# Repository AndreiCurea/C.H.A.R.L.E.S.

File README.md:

# C.H.A.R.L.E.S.
Combustion Hazzard Autonomous Robot for Localization and Environmental Scanning

A hobby project of mine that involves building up an exploration robot from scratch, using different types of technologies. The purpose of this project is to monitor VOCs and other harmful gases in office/industrial buildings, while also creating a map of the surroundings to plot the acquired data on it.

I desired it to have LiDAR, ROS implementation, main computer board and high modularity when it comes to the electrical/mechanical parts.

It has custom PCBs, custom 3D parts, and code for the microcontrollers and the main computer.

Currently, the project only works remote controlled, as I've yet to develop the automation part of the code.

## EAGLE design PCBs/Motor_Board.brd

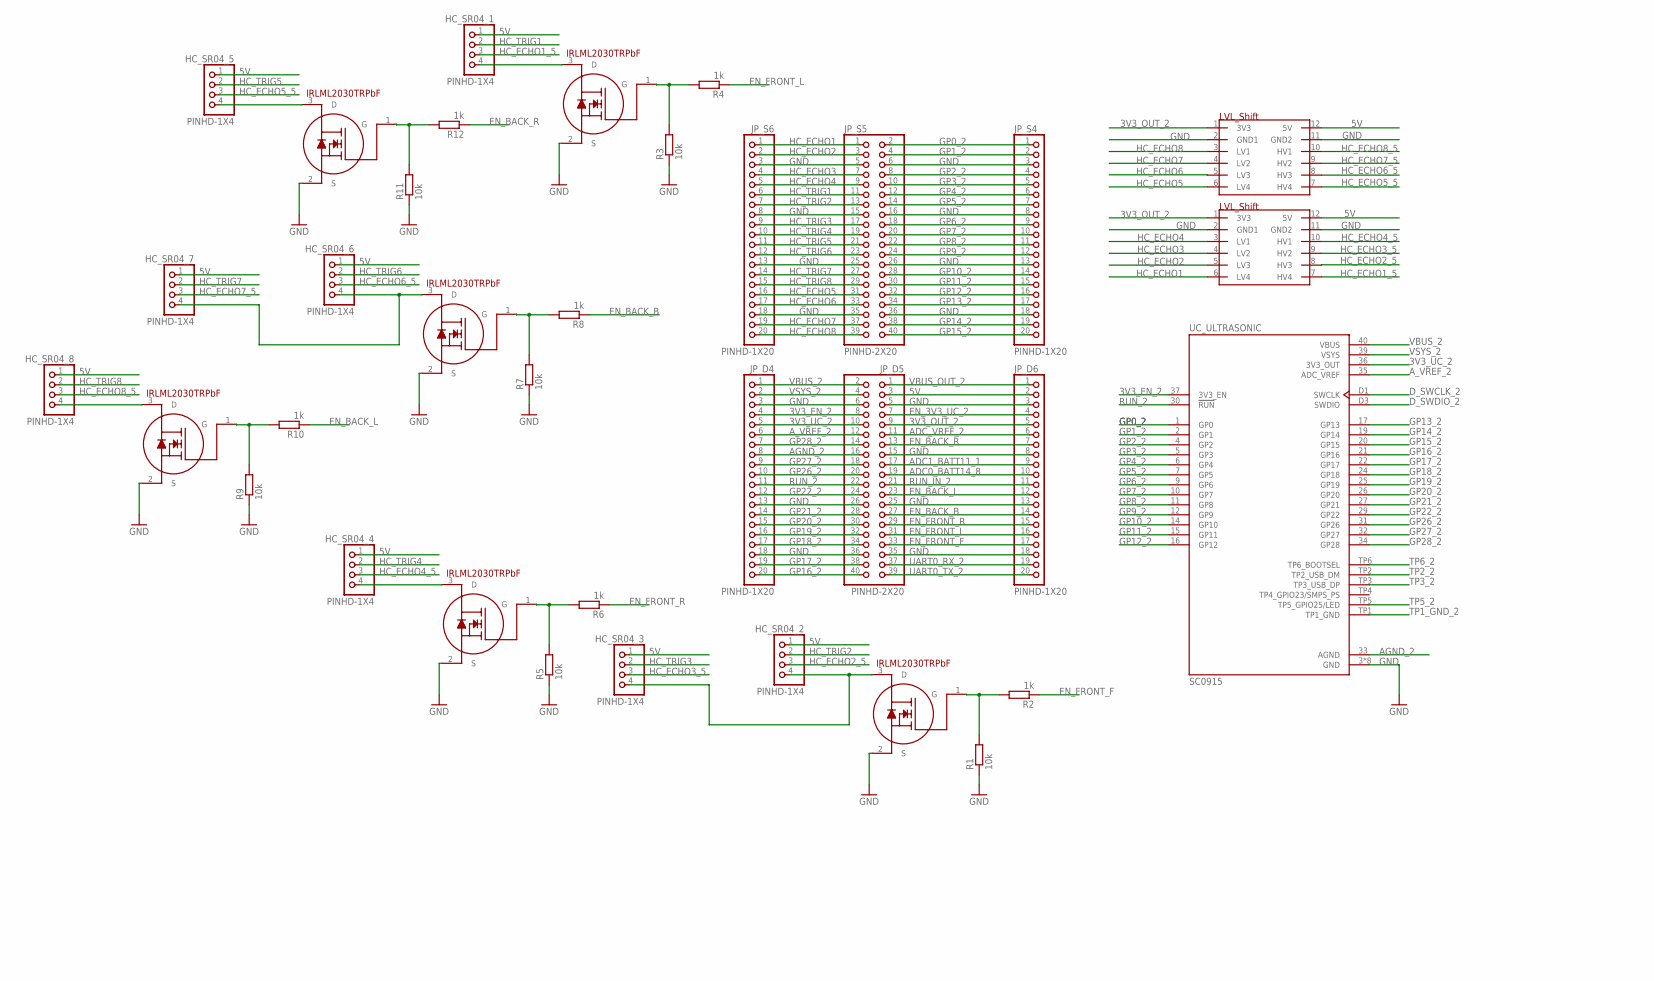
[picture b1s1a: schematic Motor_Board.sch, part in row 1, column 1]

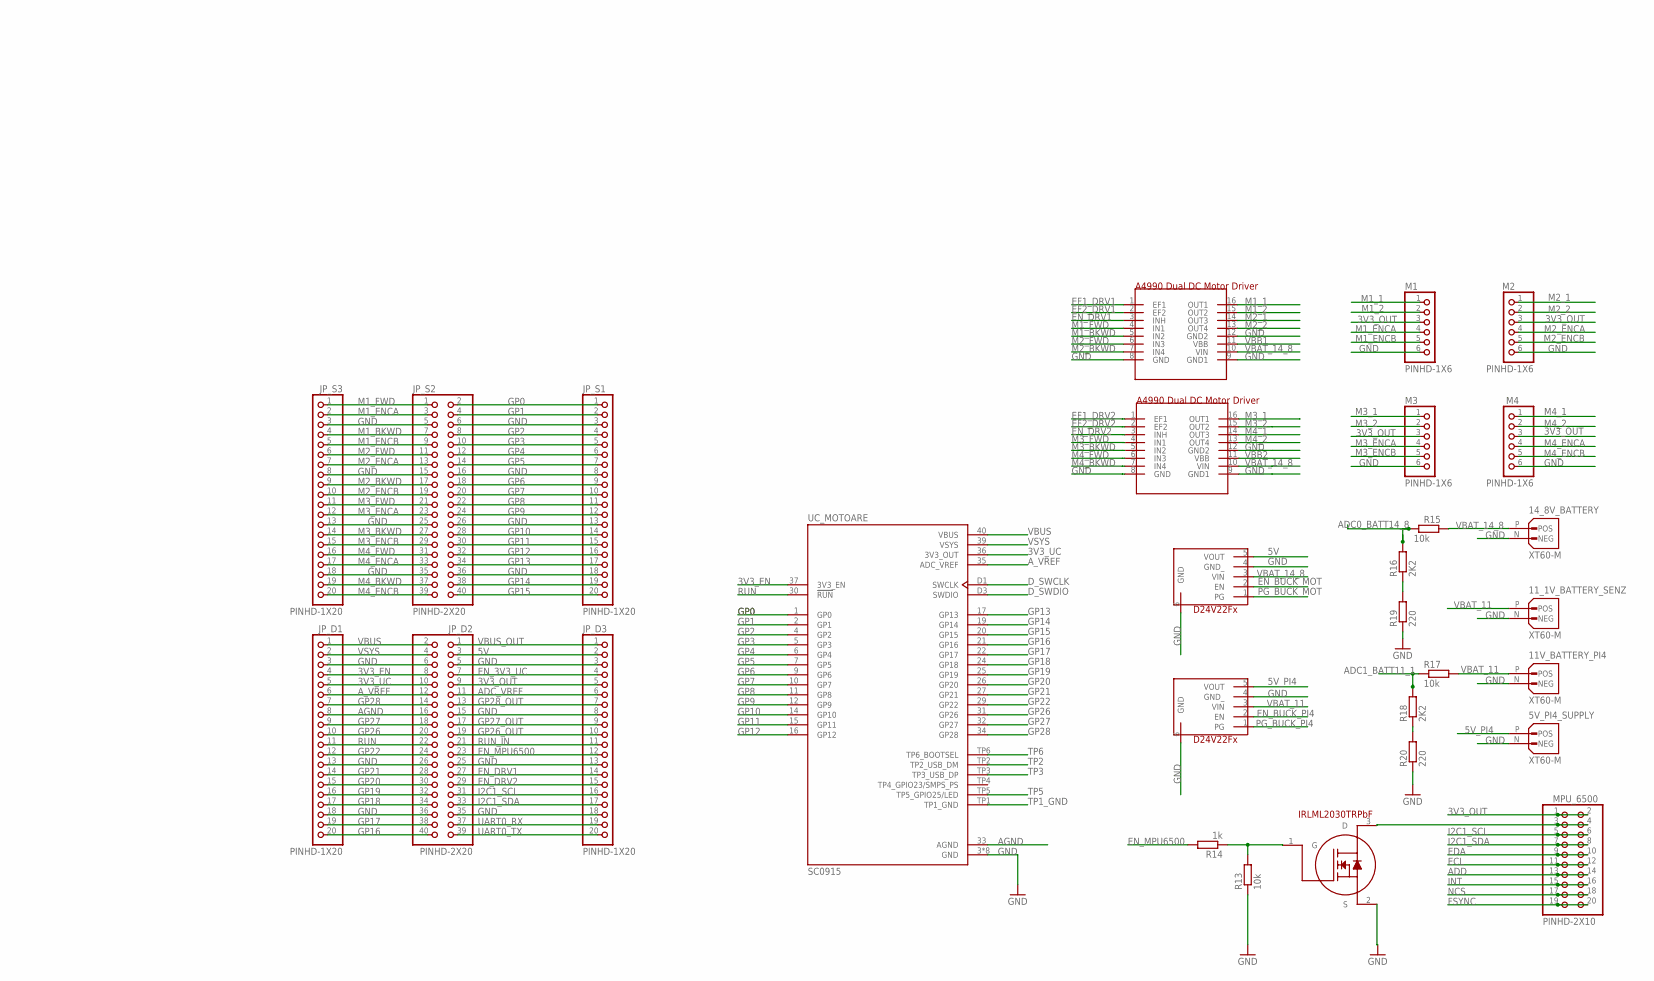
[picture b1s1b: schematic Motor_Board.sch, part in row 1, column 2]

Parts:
5V_PI4_SUPPLY, 11V_BATTERY_PI4, 11_1V_BATTERY_SENZ, 14_8V_BATTERY: XT60-M; AMASS_XT60-M
BUCK_5V, BUCK_5V1: POLOLU_BUCK_CONVERTER; POLOLU_BUCK_FOOTPRINT
DRV1, DRV2: A4990_DUAL; A4990_FOOTPRINT
HC_SR04_1, HC_SR04_2, HC_SR04_3, HC_SR04_4, HC_SR04_5, HC_SR04_6, HC_SR04_7, HC_SR04_8: PINHD-1X4; 1X04
JP_D1, JP_D3, JP_D4, JP_D6: PINHD-1X20; 1X20
JP_D2, JP_D5: PINHD-2X20; 2X20
JP_S1, JP_S3, JP_S4, JP_S6: PINHD-1X20; 1X20
JP_S2, JP_S5: PINHD-2X20; 2X20
M1, M2, M3, M4: PINHD-1X6; 1X06
MPU_6500: PINHD-2X10; 2X10
R1, R3, R5, R7, R9, R11, R13, R15, R17: 10k; R0805
R2, R4, R6, R8, R10, R12, R14: 1k; R0805
R16, R18: 2K2; R0805
R19, R20: 220; R0805
U$1, U$2: 4_CH_BIDIRECTIONAL_LVL_SHIFTER; LVL_SHIFT_FOOTPRINT
U$8, U$9, U$10, U$11, U$12, U$13, U$14: IRLML2030TRBRBF_NMOS; IRLML2030TRPBF_FOOTPRINT
UC_MOTOARE: SC0915; MODULE_SC0915
UC_ULTRASONIC: SC0915; MODULE_SC0915

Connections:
3V3_EN: JP_D1.4, JP_D2.8, UC_MOTOARE.37 (3V3_EN)
3V3_EN_2: JP_D4.4, JP_D5.8, UC_ULTRASONIC.37 (3V3_EN)
3V3_OUT: JP_D2.9, JP_D3.5, M1.3, M2.3, M3.3, M4.3, MPU_6500.1, MPU_6500.2
3V3_OUT_2: JP_D5.9, JP_D6.5, U$1.1 (3V3), U$2.1 (3V3)
3V3_UC: JP_D1.5, JP_D2.10, UC_MOTOARE.36 (3V3_OUT)
3V3_UC_2: JP_D4.5, JP_D5.10, UC_ULTRASONIC.36 (3V3_OUT)
5V: BUCK_5V.5 (VOUT), HC_SR04_1.1, HC_SR04_2.1, HC_SR04_3.1, HC_SR04_4.1, HC_SR04_5.1, HC_SR04_6.1, HC_SR04_7.1, HC_SR04_8.1, JP_D2.3, JP_D3.2, JP_D5.3, JP_D6.2, U$1.12 (5V), U$2.12 (5V)
5V_PI4: 5V_PI4_SUPPLY.P (POS), BUCK_5V1.5 (VOUT)
ADC0_BATT14_8: JP_D5.19, JP_D6.10, R15.1, R16.2
ADC1_BATT11_1: JP_D5.17, JP_D6.9, R17.1, R18.2
ADC_VREF: JP_D2.11, JP_D3.6
ADC_VREF_2: JP_D5.11, JP_D6.6
ADD: MPU_6500.13, MPU_6500.14
AGND: JP_D1.8, JP_D2.16, UC_MOTOARE.33 (AGND)
AGND_2: JP_D4.8, JP_D5.16, UC_ULTRASONIC.33 (AGND)
A_VREF: JP_D1.6, JP_D2.12, UC_MOTOARE.35 (ADC_VREF)
A_VREF_2: JP_D4.6, JP_D5.12, UC_ULTRASONIC.35 (ADC_VREF)
D_SWCLK: UC_MOTOARE.D1 (SWCLK)
D_SWCLK_2: UC_ULTRASONIC.D1 (SWCLK)
D_SWDIO: UC_MOTOARE.D3 (SWDIO)
D_SWDIO_2: UC_ULTRASONIC.D3 (SWDIO)
ECL: MPU_6500.11, MPU_6500.12
EDA: MPU_6500.9, MPU_6500.10
EF1_DRV1: DRV1.1 (EF1)
EF1_DRV2: DRV2.1 (EF1)
EF2_DRV1: DRV1.2 (EF2)
EF2_DRV2: DRV2.2 (EF2)
EN_3V3_UC: JP_D2.7, JP_D3.4
EN_3V3_UC_2: JP_D5.7, JP_D6.4
EN_BACK_B: JP_D5.27, JP_D6.14, R8.1
EN_BACK_L: JP_D5.23, JP_D6.12, R10.1
EN_BACK_R: JP_D5.13, JP_D6.7, R12.1
EN_BUCK_MOT: BUCK_5V.2 (EN)
EN_BUCK_PI4: BUCK_5V1.2 (EN)
EN_DRV1: DRV1.3 (INH), JP_D2.27, JP_D3.14
EN_DRV2: DRV2.3 (INH), JP_D2.29, JP_D3.15
EN_FRONT_F: JP_D5.33, JP_D6.17, R2.1
EN_FRONT_L: JP_D5.31, JP_D6.16, R4.1
EN_FRONT_R: JP_D5.29, JP_D6.15, R6.1
EN_MPU6500: JP_D2.23, JP_D3.12, R14.2
FSYNC: MPU_6500.19, MPU_6500.20
GND: 5V_PI4_SUPPLY.N (NEG), 11V_BATTERY_PI4.N (NEG), 11_1V_BATTERY_SENZ.N (NEG), 14_8V_BATTERY.N (NEG), BUCK_5V.4 (GND_), BUCK_5V.6 (GND), BUCK_5V1.4 (GND_), BUCK_5V1.6 (GND), DRV1.8 (GND), DRV1.9 (GND1), DRV1.12 (GND2), DRV2.8 (GND), DRV2.9 (GND1), DRV2.12 (GND2), JP_D1.3, JP_D1.13, JP_D1.18, JP_D2.5, JP_D2.6, JP_D2.15, JP_D2.25, JP_D2.26, JP_D2.35, JP_D2.36, JP_D3.3, JP_D3.8, JP_D3.13, JP_D3.18, JP_D4.3, JP_D4.13, JP_D4.18, JP_D5.5, JP_D5.6, JP_D5.15, JP_D5.25, JP_D5.26, JP_D5.35, JP_D5.36, JP_D6.3, JP_D6.8, JP_D6.13, JP_D6.18, JP_S1.3, JP_S1.8, JP_S1.13, JP_S1.18, JP_S2.5, JP_S2.6, JP_S2.15, JP_S2.16, JP_S2.25, JP_S2.26, JP_S2.35, JP_S2.36, JP_S3.3, JP_S3.8, JP_S3.13, JP_S3.18, JP_S4.3, JP_S4.8, JP_S4.13, JP_S4.18, JP_S5.5, JP_S5.6, JP_S5.15, JP_S5.16, JP_S5.25, JP_S5.26, JP_S5.35, JP_S5.36, JP_S6.3, JP_S6.8, JP_S6.13, JP_S6.18, M1.6, M2.6, M3.6, M4.6, R1.1, R3.1, R5.1, R7.1, R9.1, R11.1, R13.1, R19.1, R20.1, U$1.2 (GND1), U$1.11 (GND2), U$2.2 (GND1), U$2.11 (GND2), U$8.2 (S), U$9.2 (S), U$10.2 (S), U$11.2 (S), U$12.2 (S), U$13.2 (S), U$14.2 (S), UC_MOTOARE.3 (GND), UC_MOTOARE.8 (GND)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
GP0: JP_S1.1, JP_S2.2, UC_MOTOARE.1 (GP0)
GP0_2: JP_S4.1, JP_S5.2, UC_ULTRASONIC.1 (GP0)
GP1: JP_S1.2, JP_S2.4, UC_MOTOARE.2 (GP1)
GP1_2: JP_S4.2, JP_S5.4, UC_ULTRASONIC.2 (GP1)
GP2: JP_S1.4, JP_S2.8, UC_MOTOARE.4 (GP2)
GP2_2: JP_S4.4, JP_S5.8, UC_ULTRASONIC.4 (GP2)
GP3: JP_S1.5, JP_S2.10, UC_MOTOARE.5 (GP3)
GP3_2: JP_S4.5, JP_S5.10, UC_ULTRASONIC.5 (GP3)
GP4: JP_S1.6, JP_S2.12, UC_MOTOARE.6 (GP4)
GP4_2: JP_S4.6, JP_S5.12, UC_ULTRASONIC.6 (GP4)
GP5: JP_S1.7, JP_S2.14, UC_MOTOARE.7 (GP5)
GP5_2: JP_S4.7, JP_S5.14, UC_ULTRASONIC.7 (GP5)
GP6: JP_S1.9, JP_S2.18, UC_MOTOARE.9 (GP6)
GP6_2: JP_S4.9, JP_S5.18, UC_ULTRASONIC.9 (GP6)
GP7: JP_S1.10, JP_S2.20, UC_MOTOARE.10 (GP7)
GP7_2: JP_S4.10, JP_S5.20, UC_ULTRASONIC.10 (GP7)
GP8: JP_S1.11, JP_S2.22, UC_MOTOARE.11 (GP8)
GP8_2: JP_S4.11, JP_S5.22, UC_ULTRASONIC.11 (GP8)
GP9: JP_S1.12, JP_S2.24, UC_MOTOARE.12 (GP9)
GP9_2: JP_S4.12, JP_S5.24, UC_ULTRASONIC.12 (GP9)
GP10: JP_S1.14, JP_S2.28, UC_MOTOARE.14 (GP10)
GP10_2: JP_S4.14, JP_S5.28, UC_ULTRASONIC.14 (GP10)
GP11: JP_S1.15, JP_S2.30, UC_MOTOARE.15 (GP11)
GP11_2: JP_S4.15, JP_S5.30, UC_ULTRASONIC.15 (GP11)
GP12: JP_S1.16, JP_S2.32, UC_MOTOARE.16 (GP12)
GP12_2: JP_S4.16, JP_S5.32, UC_ULTRASONIC.16 (GP12)
GP13: JP_S1.17, JP_S2.34, UC_MOTOARE.17 (GP13)
GP13_2: JP_S4.17, JP_S5.34, UC_ULTRASONIC.17 (GP13)
GP14: JP_S1.19, JP_S2.38, UC_MOTOARE.19 (GP14)
GP14_2: JP_S4.19, JP_S5.38, UC_ULTRASONIC.19 (GP14)
GP15: JP_S1.20, JP_S2.40, UC_MOTOARE.20 (GP15)
GP15_2: JP_S4.20, JP_S5.40, UC_ULTRASONIC.20 (GP15)
GP16: JP_D1.20, JP_D2.40, UC_MOTOARE.21 (GP16)
GP16_2: JP_D4.20, JP_D5.40, UC_ULTRASONIC.21 (GP16)
GP17: JP_D1.19, JP_D2.38, UC_MOTOARE.22 (GP17)
GP17_2: JP_D4.19, JP_D5.38, UC_ULTRASONIC.22 (GP17)
GP18: JP_D1.17, JP_D2.34, UC_MOTOARE.24 (GP18)
GP18_2: JP_D4.17, JP_D5.34, UC_ULTRASONIC.24 (GP18)
GP19: JP_D1.16, JP_D2.32, UC_MOTOARE.25 (GP19)
GP19_2: JP_D4.16, JP_D5.32, UC_ULTRASONIC.25 (GP19)
GP20: JP_D1.15, JP_D2.30, UC_MOTOARE.26 (GP20)
GP20_2: JP_D4.15, JP_D5.30, UC_ULTRASONIC.26 (GP20)
GP21: JP_D1.14, JP_D2.28, UC_MOTOARE.27 (GP21)
GP21_2: JP_D4.14, JP_D5.28, UC_ULTRASONIC.27 (GP21)
GP22: JP_D1.12, JP_D2.24, UC_MOTOARE.29 (GP22)
GP22_2: JP_D4.12, JP_D5.24, UC_ULTRASONIC.29 (GP22)
GP26: JP_D1.10, JP_D2.20, UC_MOTOARE.31 (GP26)
GP26_2: JP_D4.10, JP_D5.20, UC_ULTRASONIC.31 (GP26)
GP26_OUT: JP_D2.19, JP_D3.10
GP27: JP_D1.9, JP_D2.18, UC_MOTOARE.32 (GP27)
GP27_2: JP_D4.9, JP_D5.18, UC_ULTRASONIC.32 (GP27)
GP27_OUT: JP_D2.17, JP_D3.9
GP28: JP_D1.7, JP_D2.14, UC_MOTOARE.34 (GP28)
GP28_2: JP_D4.7, JP_D5.14, UC_ULTRASONIC.34 (GP28)
GP28_OUT: JP_D2.13, JP_D3.7
HC_ECHO1: JP_S5.1, JP_S6.1, U$2.6 (LV4)
HC_ECHO1_5: HC_SR04_1.3, U$2.7 (HV4)
HC_ECHO2: JP_S5.3, JP_S6.2, U$2.5 (LV3)
HC_ECHO2_5: HC_SR04_2.3, U$2.8 (HV3)
HC_ECHO3: JP_S5.7, JP_S6.4, U$2.4 (LV2)
HC_ECHO3_5: HC_SR04_3.3, U$2.9 (HV2)
HC_ECHO4: JP_S5.9, JP_S6.5, U$2.3 (LV1)
HC_ECHO4_5: HC_SR04_4.3, U$2.10 (HV1)
HC_ECHO5: JP_S5.31, JP_S6.16, U$1.6 (LV4)
HC_ECHO5_5: HC_SR04_5.3, U$1.7 (HV4)
HC_ECHO6: JP_S5.33, JP_S6.17, U$1.5 (LV3)
HC_ECHO6_5: HC_SR04_6.3, U$1.8 (HV3)
HC_ECHO7: JP_S5.37, JP_S6.19, U$1.4 (LV2)
HC_ECHO7_5: HC_SR04_7.3, U$1.9 (HV2)
HC_ECHO8: JP_S5.39, JP_S6.20, U$1.3 (LV1)
HC_ECHO8_5: HC_SR04_8.3, U$1.10 (HV1)
HC_TRIG1: HC_SR04_1.2, JP_S5.11, JP_S6.6
HC_TRIG2: HC_SR04_2.2, JP_S5.13, JP_S6.7
HC_TRIG3: HC_SR04_3.2, JP_S5.17, JP_S6.9
HC_TRIG4: HC_SR04_4.2, JP_S5.19, JP_S6.10
HC_TRIG5: HC_SR04_5.2, JP_S5.21, JP_S6.11
HC_TRIG6: HC_SR04_6.2, JP_S5.23, JP_S6.12
HC_TRIG7: HC_SR04_7.2, JP_S5.27, JP_S6.14
HC_TRIG8: HC_SR04_8.2, JP_S5.29, JP_S6.15
I2C1_SCL: JP_D2.31, JP_D3.16, MPU_6500.5, MPU_6500.6
I2C1_SDA: JP_D2.33, JP_D3.17, MPU_6500.7, MPU_6500.8
INT: MPU_6500.15, MPU_6500.16
M1_1: DRV1.16 (OUT1), M1.1
M1_2: DRV1.15 (OUT2), M1.2
M1_BKWD: DRV1.5 (IN2), JP_S2.7, JP_S3.4
M1_ENCA: JP_S2.3, JP_S3.2, M1.4
M1_ENCB: JP_S2.9, JP_S3.5, M1.5
M1_FWD: DRV1.4 (IN1), JP_S2.1, JP_S3.1
M2_1: DRV1.14 (OUT3), M2.1
M2_2: DRV1.13 (OUT4), M2.2
M2_BKWD: DRV1.7 (IN4), JP_S2.17, JP_S3.9
M2_ENCA: JP_S2.13, JP_S3.7, M2.4
M2_ENCB: JP_S2.19, JP_S3.10, M2.5
M2_FWD: DRV1.6 (IN3), JP_S2.11, JP_S3.6
M3_1: DRV2.16 (OUT1), M3.1
M3_2: DRV2.15 (OUT2), M3.2
M3_BKWD: DRV2.5 (IN2), JP_S2.27, JP_S3.14
M3_ENCA: JP_S2.23, JP_S3.12, M3.4
M3_ENCB: JP_S2.29, JP_S3.15, M3.5
M3_FWD: DRV2.4 (IN1), JP_S2.21, JP_S3.11
M4_1: DRV2.14 (OUT3), M4.1
M4_2: DRV2.13 (OUT4), M4.2
M4_BKWD: DRV2.7 (IN4), JP_S2.37, JP_S3.19
M4_ENCA: JP_S2.33, JP_S3.17, M4.4
M4_ENCB: JP_S2.39, JP_S3.20, M4.5
M4_FWD: DRV2.6 (IN3), JP_S2.31, JP_S3.16
unnamed: HC_SR04_1.4, U$9.3 (D)
unnamed: R3.2, R4.2, U$9.1 (G)
unnamed: HC_SR04_2.4, HC_SR04_3.4, U$10.3 (D)
unnamed: R1.2, R2.2, U$10.1 (G)
unnamed: HC_SR04_4.4, U$11.3 (D)
unnamed: R5.2, R6.2, U$11.1 (G)
unnamed: HC_SR04_5.4, U$12.3 (D)
unnamed: R11.2, R12.2, U$12.1 (G)
unnamed: R7.2, R8.2, U$13.1 (G)
unnamed: HC_SR04_6.4, HC_SR04_7.4, U$13.3 (D)
unnamed: HC_SR04_8.4, U$14.3 (D)
unnamed: R9.2, R10.2, U$14.1 (G)
unnamed: MPU_6500.3, MPU_6500.4, U$8.3 (D)
unnamed: R13.2, R14.1, U$8.1 (G)
unnamed: R16.1, R19.2
unnamed: R18.1, R20.2
NCS: MPU_6500.17, MPU_6500.18
PG_BUCK_MOT: BUCK_5V.1 (PG)
PG_BUCK_PI4: BUCK_5V1.1 (PG)
RUN: JP_D1.11, JP_D2.22, UC_MOTOARE.30 (!RUN)
RUN_2: JP_D4.11, JP_D5.22, UC_ULTRASONIC.30 (!RUN)
RUN_IN: JP_D2.21, JP_D3.11
RUN_IN_2: JP_D5.21, JP_D6.11
TP1_GND: UC_MOTOARE.TP1 (TP1_GND)
TP1_GND_2: UC_ULTRASONIC.TP1 (TP1_GND)
TP2: UC_MOTOARE.TP2 (TP2_USB_DM)
TP2_2: UC_ULTRASONIC.TP2 (TP2_USB_DM)
TP3: UC_MOTOARE.TP3 (TP3_USB_DP)
TP3_2: UC_ULTRASONIC.TP3 (TP3_USB_DP)
TP5: UC_MOTOARE.TP5 (TP5_GPIO25/LED)
TP5_2: UC_ULTRASONIC.TP5 (TP5_GPIO25/LED)
TP6: UC_MOTOARE.TP6 (TP6_BOOTSEL)
TP6_2: UC_ULTRASONIC.TP6 (TP6_BOOTSEL)
UART0_RX: JP_D2.37, JP_D3.19
UART0_RX_2: JP_D5.37, JP_D6.19
UART0_TX: JP_D2.39, JP_D3.20
UART0_TX_2: JP_D5.39, JP_D6.20
VBAT_11: 11V_BATTERY_PI4.P (POS), 11_1V_BATTERY_SENZ.P (POS), BUCK_5V1.3 (VIN), R17.2
VBAT_14_8: 14_8V_BATTERY.P (POS), BUCK_5V.3 (VIN), DRV1.10 (VIN), DRV2.10 (VIN), R15.2
VBB1: DRV1.11 (VBB)
VBB2: DRV2.11 (VBB)
VBUS: JP_D1.1, JP_D2.2, UC_MOTOARE.40 (VBUS)
VBUS_2: JP_D4.1, JP_D5.2, UC_ULTRASONIC.40 (VBUS)
VBUS_OUT: JP_D2.1, JP_D3.1
VBUS_OUT_2: JP_D5.1, JP_D6.1
VSYS: JP_D1.2, JP_D2.4, UC_MOTOARE.39 (VSYS)
VSYS_2: JP_D4.2, JP_D5.4, UC_ULTRASONIC.39 (VSYS)

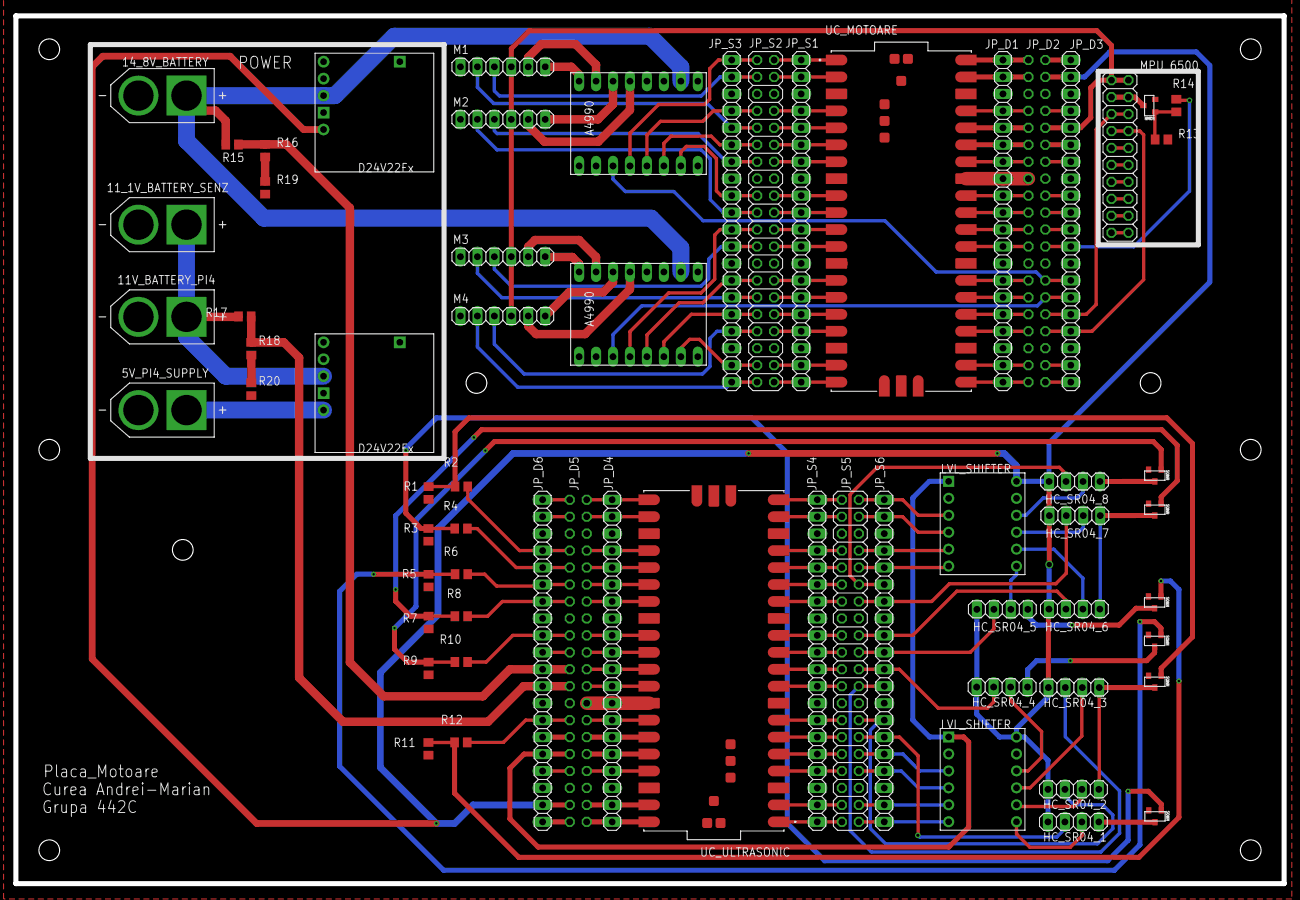
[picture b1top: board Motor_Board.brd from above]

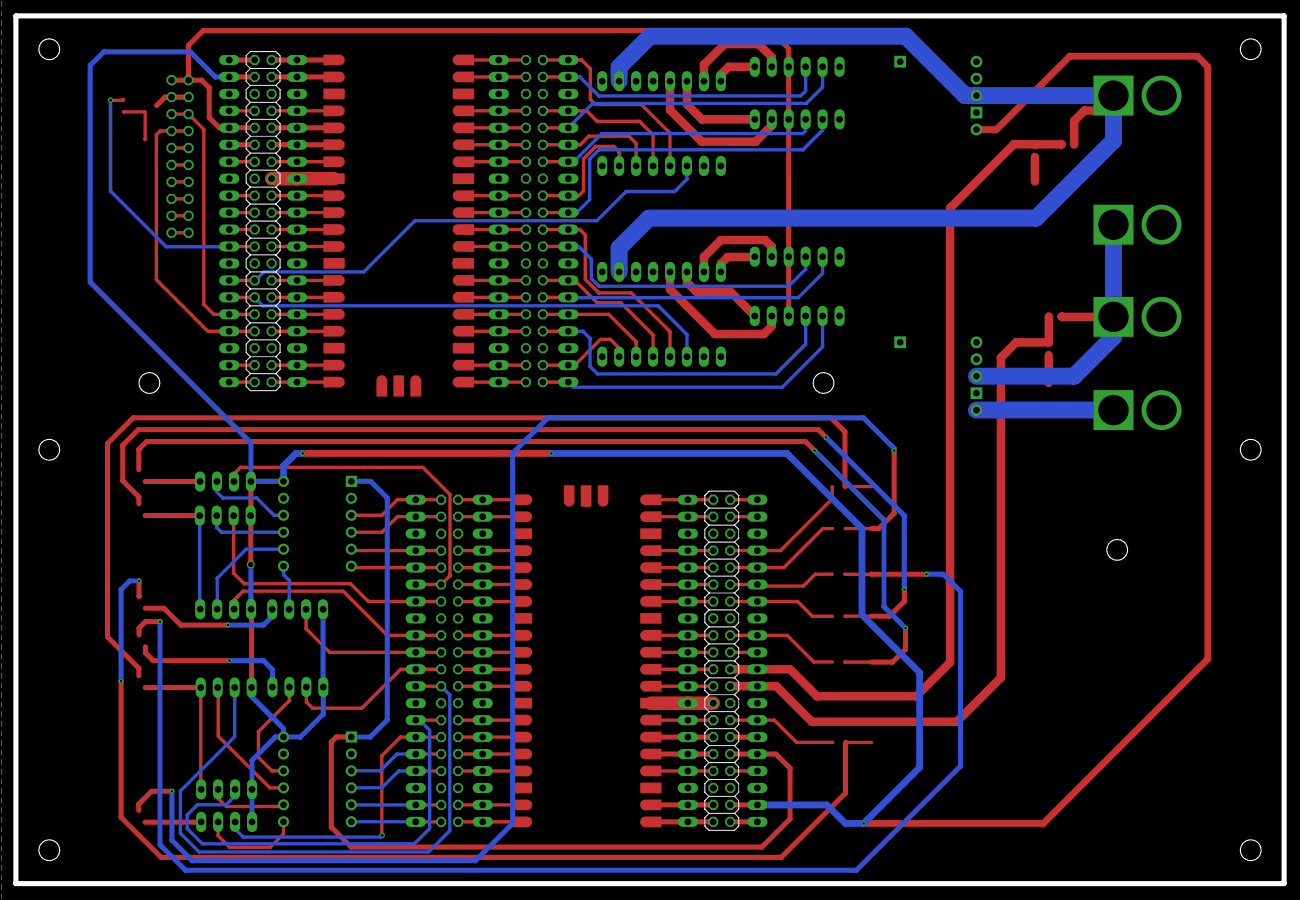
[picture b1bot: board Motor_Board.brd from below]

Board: 2 copper layers, 190.0 x 130.0 mm, 64 parts (2 on the bottom side), 171 nets.

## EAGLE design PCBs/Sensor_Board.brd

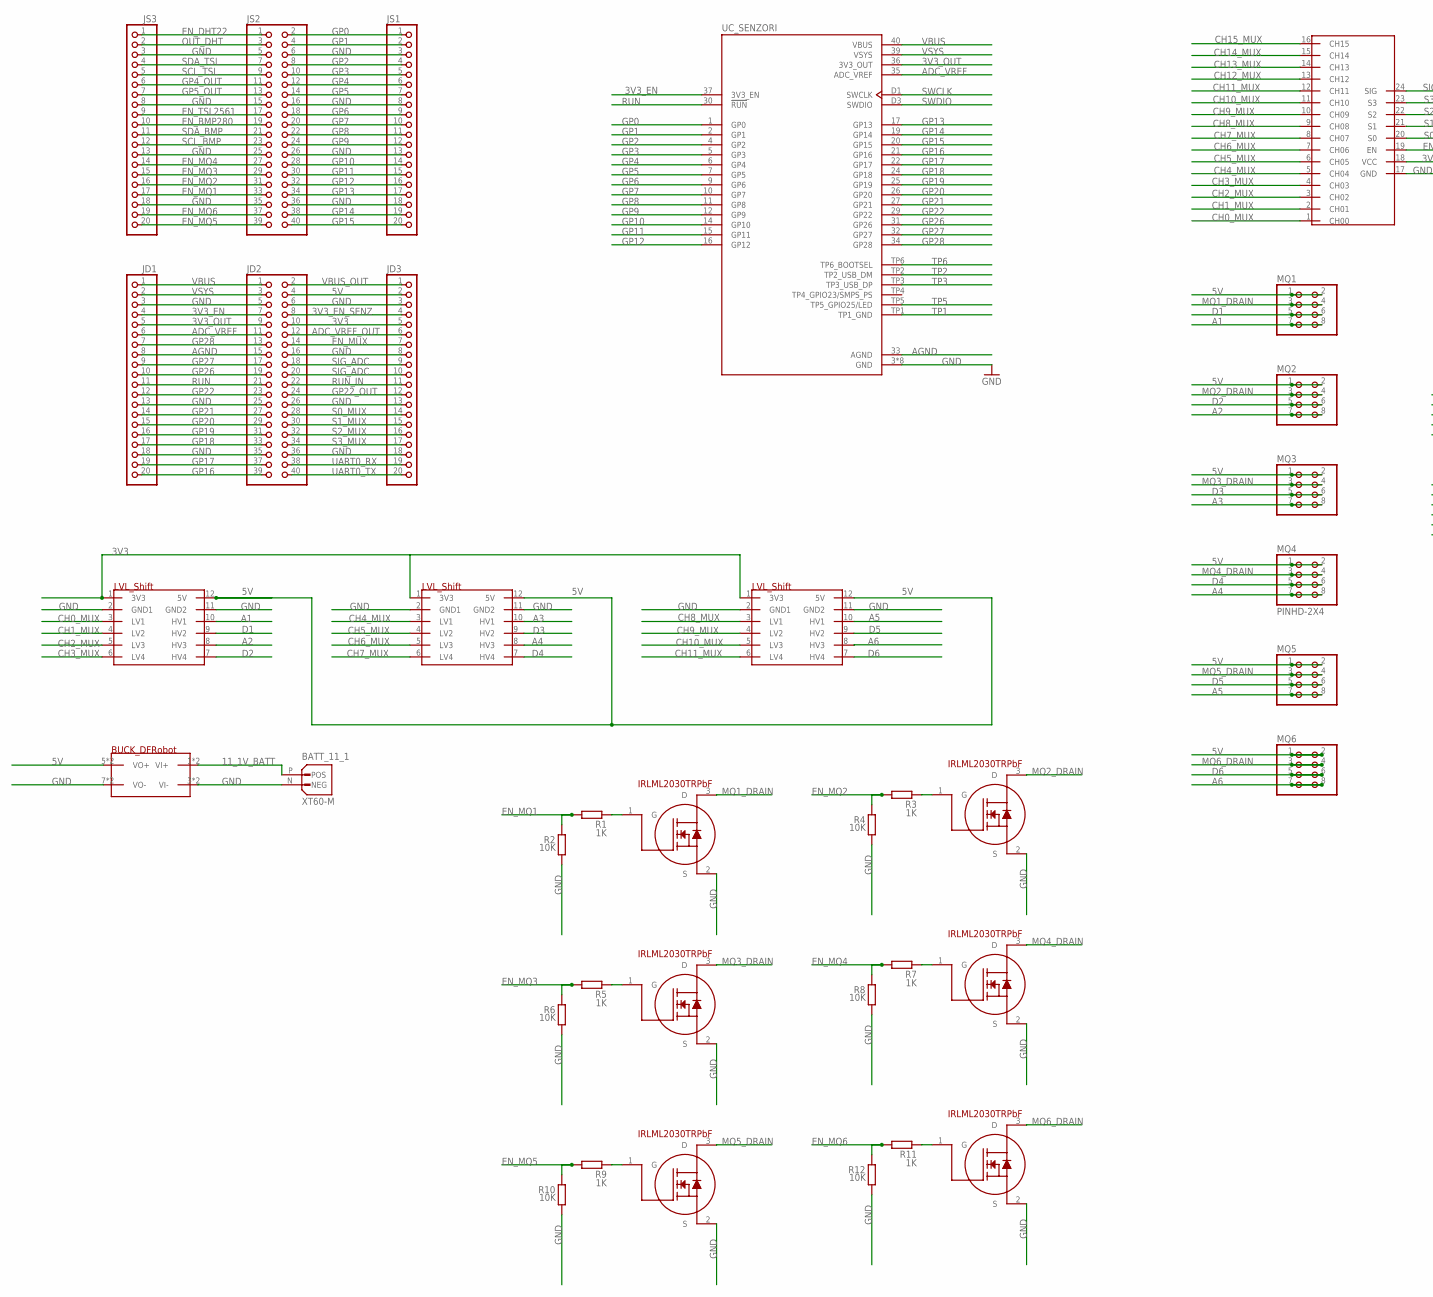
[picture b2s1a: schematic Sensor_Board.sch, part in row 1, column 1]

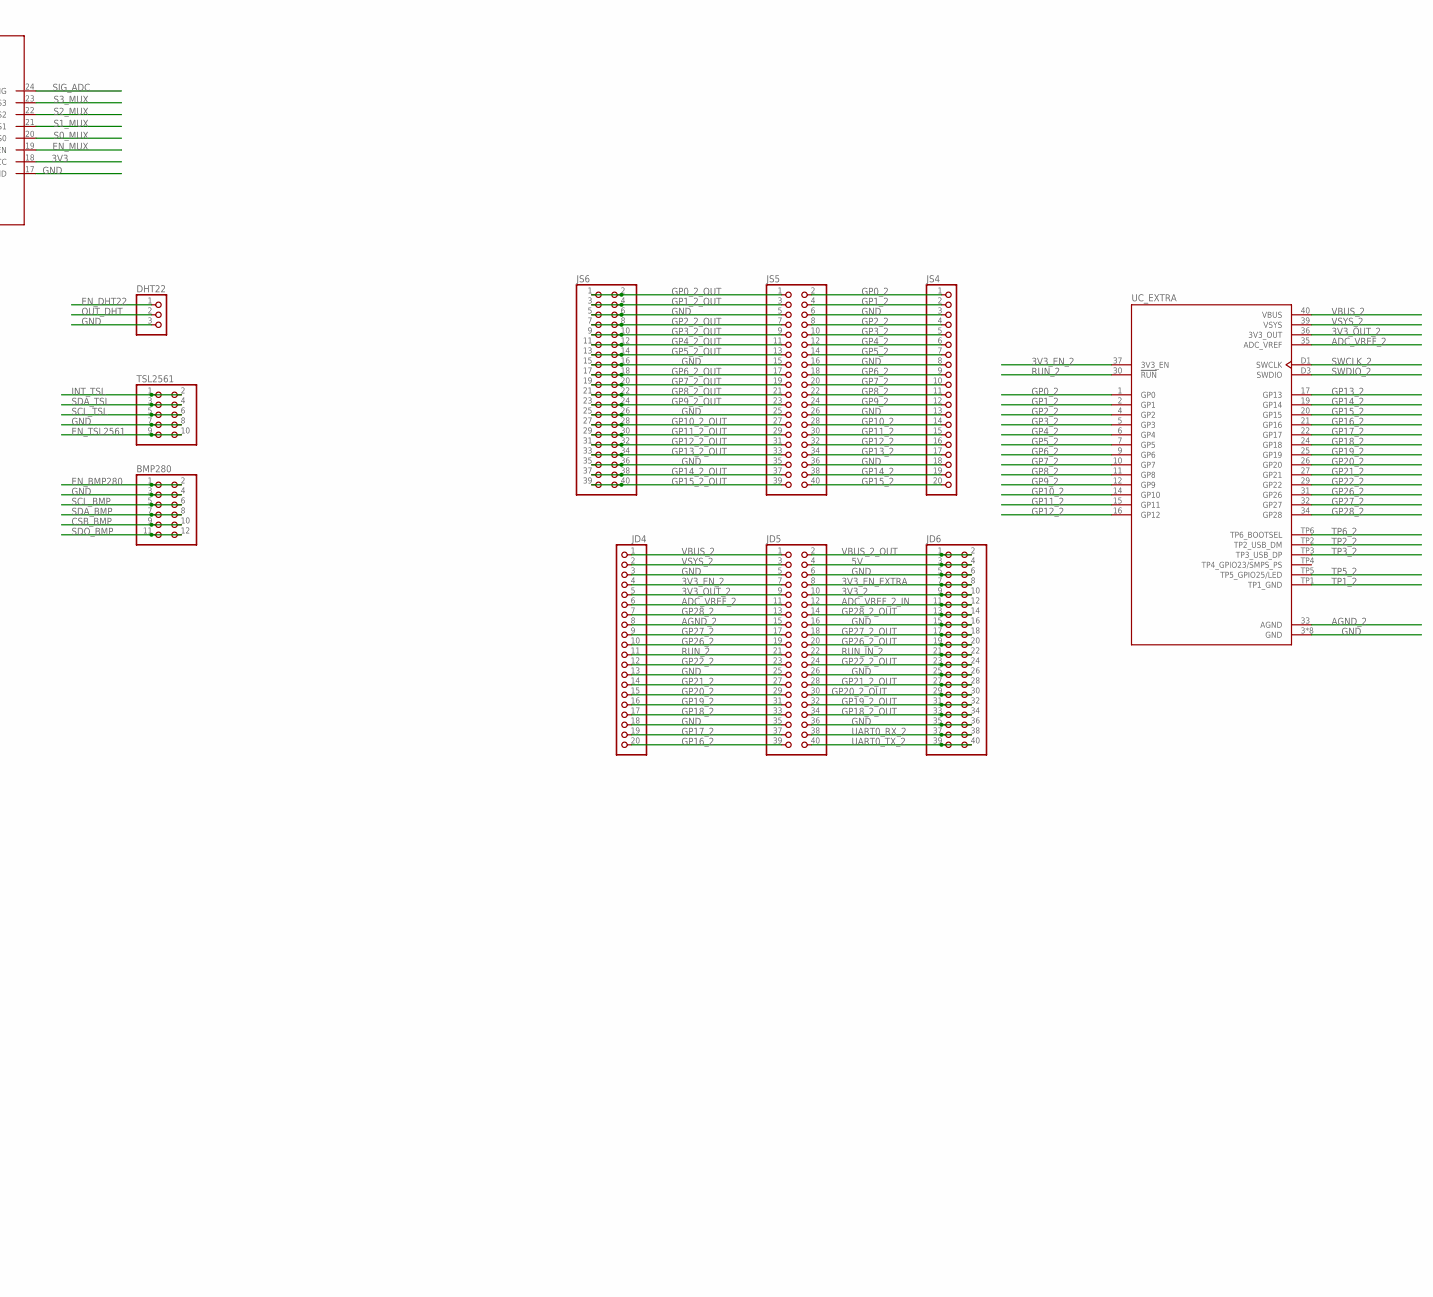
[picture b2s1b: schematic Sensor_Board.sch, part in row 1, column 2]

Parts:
BATT_11_1: XT60-M; AMASS_XT60-M
BMP280: PINHD-2X6; 2X06
DHT22: PINHD-1X3; 1X03
JD1, JD3, JD4: PINHD-1X20; 1X20
JD2, JD5, JD6: PINHD-2X20; 2X20
JS1, JS3, JS4: PINHD-1X20; 1X20
JS2, JS5, JS6: PINHD-2X20; 2X20
MQ1, MQ2, MQ3, MQ4, MQ5, MQ6: PINHD-2X4; 2X04
MUX: CD74HC4067_MUX; 16_CH_MUX_FOOTPRINT
R1, R3, R5, R7, R9, R11: 1K; R0805
R2, R4, R6, R8, R10, R12: 10K; R0805
TSL2561: PINHD-2X5; 2X05
U$1, U$7, U$8, U$9, U$10, U$11: IRLML2030TRBRBF_NMOS; IRLML2030TRPBF_FOOTPRINT
U$2, U$3, U$4: 4_CH_BIDIRECTIONAL_LVL_SHIFTER; LVL_SHIFT_FOOTPRINT
U$5: DFROBOT_BUCK_CONVERTER; DFROBOT_BUCK_FOOTPRINT
UC_EXTRA: SC0915; MODULE_SC0915
UC_SENZORI: SC0915; MODULE_SC0915

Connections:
3V3: JD2.10, JD3.5, MUX.18 (VCC), U$2.1 (3V3), U$3.1 (3V3), U$4.1 (3V3)
3V3_2: JD5.10, JD6.9, JD6.10
3V3_EN: JD1.4, JD2.7, UC_SENZORI.37 (3V3_EN)
3V3_EN_2: JD4.4, JD5.7, UC_EXTRA.37 (3V3_EN)
3V3_EN_EXTRA: JD5.8, JD6.7, JD6.8
3V3_EN_SENZ: JD2.8, JD3.4
3V3_OUT: JD1.5, JD2.9, UC_SENZORI.36 (3V3_OUT)
3V3_OUT_2: JD4.5, JD5.9, UC_EXTRA.36 (3V3_OUT)
5V: JD2.4, JD3.2, JD5.4, JD6.3, JD6.4, MQ1.1, MQ1.2, MQ2.1, MQ2.2, MQ3.1, MQ3.2, MQ4.1, MQ4.2, MQ5.1, MQ5.2, MQ6.1, MQ6.2, U$2.12 (5V), U$3.12 (5V), U$4.12 (5V), U$5.5 (VO+), U$5.6 (VO+)
11_1V_BATT: BATT_11_1.P (POS), U$5.1 (VI+), U$5.2 (VI+)
A1: MQ1.7, MQ1.8, U$2.10 (HV1)
A2: MQ2.7, MQ2.8, U$2.8 (HV3)
A3: MQ3.7, MQ3.8, U$3.10 (HV1)
A4: MQ4.7, MQ4.8, U$3.8 (HV3)
A5: MQ5.7, MQ5.8, U$4.10 (HV1)
A6: MQ6.7, MQ6.8, U$4.8 (HV3)
ADC_VREF: JD1.6, JD2.11, UC_SENZORI.35 (ADC_VREF)
ADC_VREF_2: JD4.6, JD5.11, UC_EXTRA.35 (ADC_VREF)
ADC_VREF_2_IN: JD5.12, JD6.11, JD6.12
ADC_VREF_OUT: JD2.12, JD3.6
AGND: JD1.8, JD2.15, UC_SENZORI.33 (AGND)
AGND_2: JD4.8, JD5.15, UC_EXTRA.33 (AGND)
CH0_MUX: MUX.1 (CH00), U$2.3 (LV1)
CH1_MUX: MUX.2 (CH01), U$2.4 (LV2)
CH2_MUX: MUX.3 (CH02), U$2.5 (LV3)
CH3_MUX: MUX.4 (CH03), U$2.6 (LV4)
CH4_MUX: MUX.5 (CH04), U$3.3 (LV1)
CH5_MUX: MUX.6 (CH05), U$3.4 (LV2)
CH6_MUX: MUX.7 (CH06), U$3.5 (LV3)
CH7_MUX: MUX.8 (CH07), U$3.6 (LV4)
CH8_MUX: MUX.9 (CH08), U$4.3 (LV1)
CH9_MUX: MUX.10 (CH09), U$4.4 (LV2)
CH10_MUX: MUX.11 (CH10), U$4.5 (LV3)
CH11_MUX: MUX.12 (CH11), U$4.6 (LV4)
CH12_MUX: MUX.13 (CH12)
CH13_MUX: MUX.14 (CH13)
CH14_MUX: MUX.15 (CH14)
CH15_MUX: MUX.16 (CH15)
CSB_BMP: BMP280.9, BMP280.10
D1: MQ1.5, MQ1.6, U$2.9 (HV2)
D2: MQ2.5, MQ2.6, U$2.7 (HV4)
D3: MQ3.5, MQ3.6, U$3.9 (HV2)
D4: MQ4.5, MQ4.6, U$3.7 (HV4)
D5: MQ5.5, MQ5.6, U$4.9 (HV2)
D6: MQ6.5, MQ6.6, U$4.7 (HV4)
EN_BMP280: BMP280.1, BMP280.2, JS2.19, JS3.10
EN_DHT22: DHT22.1, JS2.1, JS3.1
EN_MQ1: JS2.33, JS3.17, R1.2, R2.2
EN_MQ2: JS2.31, JS3.16, R3.2, R4.2
EN_MQ3: JS2.29, JS3.15, R5.2, R6.2
EN_MQ4: JS2.27, JS3.14, R7.2, R8.2
EN_MQ5: JS2.39, JS3.20, R9.2, R10.2
EN_MQ6: JS2.37, JS3.19, R11.2, R12.2
EN_MUX: JD2.14, JD3.7, MUX.19 (EN)
EN_TSL2561: JS2.17, JS3.9, TSL2561.9, TSL2561.10
GND: BATT_11_1.N (NEG), BMP280.3, BMP280.4, DHT22.3, JD1.3, JD1.13, JD1.18, JD2.5, JD2.6, JD2.16, JD2.25, JD2.26, JD2.35, JD2.36, JD3.3, JD3.8, JD3.13, JD3.18, JD4.3, JD4.13, JD4.18, JD5.5, JD5.6, JD5.16, JD5.25, JD5.26, JD5.35, JD5.36, JD6.5, JD6.6, JD6.15, JD6.16, JD6.25, JD6.26, JD6.35, JD6.36, JS1.3, JS1.8, JS1.13, JS1.18, JS2.5, JS2.6, JS2.15, JS2.16, JS2.25, JS2.26, JS2.35, JS2.36, JS3.3, JS3.8, JS3.13, JS3.18, JS4.3, JS4.8, JS4.13, JS4.18, JS5.5, JS5.6, JS5.15, JS5.16, JS5.25, JS5.26, JS5.35, JS5.36, JS6.5, JS6.6, JS6.15, JS6.16, JS6.25, JS6.26, JS6.35, JS6.36, MUX.17 (GND), R2.1, R4.1, R6.1, R8.1, R10.1, R12.1, TSL2561.7, TSL2561.8, U$1.2 (S), U$2.2 (GND1), U$2.11 (GND2), U$3.2 (GND1), U$3.11 (GND2), U$4.2 (GND1), U$4.11 (GND2), U$5.3 (VI-), U$5.4 (VI-), U$5.7 (VO-), U$5.8 (VO-), U$7.2 (S), U$8.2 (S), U$9.2 (S), U$10.2 (S), U$11.2 (S), UC_EXTRA.3 (GND), UC_EXTRA.8 (GND), UC_EXTRA.13 (GND)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
GP0: JS1.1, JS2.2, UC_SENZORI.1 (GP0)
GP0_2: JS4.1, JS5.2, UC_EXTRA.1 (GP0)
GP0_2_OUT: JS5.1, JS6.1, JS6.2
GP1: JS1.2, JS2.4, UC_SENZORI.2 (GP1)
GP1_2: JS4.2, JS5.4, UC_EXTRA.2 (GP1)
GP1_2_OUT: JS5.3, JS6.3, JS6.4
GP2: JS1.4, JS2.8, UC_SENZORI.4 (GP2)
GP2_2: JS4.4, JS5.8, UC_EXTRA.4 (GP2)
GP2_2_OUT: JS5.7, JS6.7, JS6.8
GP3: JS1.5, JS2.10, UC_SENZORI.5 (GP3)
GP3_2: JS4.5, JS5.10, UC_EXTRA.5 (GP3)
GP3_2_OUT: JS5.9, JS6.9, JS6.10
GP4: JS1.6, JS2.12, UC_SENZORI.6 (GP4)
GP4_2: JS4.6, JS5.12, UC_EXTRA.6 (GP4)
GP4_2_OUT: JS5.11, JS6.11, JS6.12
GP4_OUT: JS2.11, JS3.6
GP5: JS1.7, JS2.14, UC_SENZORI.7 (GP5)
GP5_2: JS4.7, JS5.14, UC_EXTRA.7 (GP5)
GP5_2_OUT: JS5.13, JS6.13, JS6.14
GP5_OUT: JS2.13, JS3.7
GP6: JS1.9, JS2.18, UC_SENZORI.9 (GP6)
GP6_2: JS4.9, JS5.18, UC_EXTRA.9 (GP6)
GP6_2_OUT: JS5.17, JS6.17, JS6.18
GP7: JS1.10, JS2.20, UC_SENZORI.10 (GP7)
GP7_2: JS4.10, JS5.20, UC_EXTRA.10 (GP7)
GP7_2_OUT: JS5.19, JS6.19, JS6.20
GP8: JS1.11, JS2.22, UC_SENZORI.11 (GP8)
GP8_2: JS4.11, JS5.22, UC_EXTRA.11 (GP8)
GP8_2_OUT: JS5.21, JS6.21, JS6.22
GP9: JS1.12, JS2.24, UC_SENZORI.12 (GP9)
GP9_2: JS4.12, JS5.24, UC_EXTRA.12 (GP9)
GP9_2_OUT: JS5.23, JS6.23, JS6.24
GP10: JS1.14, JS2.28, UC_SENZORI.14 (GP10)
GP10_2: JS4.14, JS5.28, UC_EXTRA.14 (GP10)
GP10_2_OUT: JS5.27, JS6.27, JS6.28
GP11: JS1.15, JS2.30, UC_SENZORI.15 (GP11)
GP11_2: JS4.15, JS5.30, UC_EXTRA.15 (GP11)
GP11_2_OUT: JS5.29, JS6.29, JS6.30
GP12: JS1.16, JS2.32, UC_SENZORI.16 (GP12)
GP12_2: JS4.16, JS5.32, UC_EXTRA.16 (GP12)
GP12_2_OUT: JS5.31, JS6.31, JS6.32
GP13: JS1.17, JS2.34, UC_SENZORI.17 (GP13)
GP13_2: JS4.17, JS5.34, UC_EXTRA.17 (GP13)
GP13_2_OUT: JS5.33, JS6.33, JS6.34
GP14: JS1.19, JS2.38, UC_SENZORI.19 (GP14)
GP14_2: JS4.19, JS5.38, UC_EXTRA.19 (GP14)
GP14_2_OUT: JS5.37, JS6.37, JS6.38
GP15: JS1.20, JS2.40, UC_SENZORI.20 (GP15)
GP15_2: JS4.20, JS5.40, UC_EXTRA.20 (GP15)
GP15_2_OUT: JS5.39, JS6.39, JS6.40
GP16: JD1.20, JD2.39, UC_SENZORI.21 (GP16)
GP16_2: JD4.20, JD5.39, UC_EXTRA.21 (GP16)
GP17: JD1.19, JD2.37, UC_SENZORI.22 (GP17)
GP17_2: JD4.19, JD5.37, UC_EXTRA.22 (GP17)
GP18: JD1.17, JD2.33, UC_SENZORI.24 (GP18)
GP18_2: JD4.17, JD5.33, UC_EXTRA.24 (GP18)
GP18_2_OUT: JD5.34, JD6.33, JD6.34
GP19: JD1.16, JD2.31, UC_SENZORI.25 (GP19)
GP19_2: JD4.16, JD5.31, UC_EXTRA.25 (GP19)
GP19_2_OUT: JD5.32, JD6.31, JD6.32
GP20: JD1.15, JD2.29, UC_SENZORI.26 (GP20)
GP20_2: JD4.15, JD5.29, UC_EXTRA.26 (GP20)
GP20_2_OUT: JD5.30, JD6.29, JD6.30
GP21: JD1.14, JD2.27, UC_SENZORI.27 (GP21)
GP21_2: JD4.14, JD5.27, UC_EXTRA.27 (GP21)
GP21_2_OUT: JD5.28, JD6.27, JD6.28
GP22: JD1.12, JD2.23, UC_SENZORI.29 (GP22)
GP22_2: JD4.12, JD5.23, UC_EXTRA.29 (GP22)
GP22_2_OUT: JD5.24, JD6.23, JD6.24
GP22_OUT: JD2.24, JD3.12
GP26: JD1.10, JD2.19, UC_SENZORI.31 (GP26)
GP26_2: JD4.10, JD5.19, UC_EXTRA.31 (GP26)
GP26_2_OUT: JD5.20, JD6.19, JD6.20
GP27: JD1.9, JD2.17, UC_SENZORI.32 (GP27)
GP27_2: JD4.9, JD5.17, UC_EXTRA.32 (GP27)
GP27_2_OUT: JD5.18, JD6.17, JD6.18
GP28: JD1.7, JD2.13, UC_SENZORI.34 (GP28)
GP28_2: JD4.7, JD5.13, UC_EXTRA.34 (GP28)
GP28_2_OUT: JD5.14, JD6.13, JD6.14
INT_TSL: TSL2561.1, TSL2561.2
MQ1_DRAIN: MQ1.3, MQ1.4, U$1.3 (D)
MQ2_DRAIN: MQ2.3, MQ2.4, U$7.3 (D)
MQ3_DRAIN: MQ3.3, MQ3.4, U$8.3 (D)
MQ4_DRAIN: MQ4.3, MQ4.4, U$9.3 (D)
MQ5_DRAIN: MQ5.3, MQ5.4, U$10.3 (D)
MQ6_DRAIN: MQ6.3, MQ6.4, U$11.3 (D)
unnamed: R1.1, U$1.1 (G)
unnamed: R3.1, U$7.1 (G)
unnamed: R5.1, U$8.1 (G)
unnamed: R7.1, U$9.1 (G)
unnamed: R9.1, U$10.1 (G)
unnamed: R11.1, U$11.1 (G)
OUT_DHT: DHT22.2, JS2.3, JS3.2
RUN: JD1.11, JD2.21, UC_SENZORI.30 (!RUN)
RUN_2: JD4.11, JD5.21, UC_EXTRA.30 (!RUN)
RUN_IN: JD2.22, JD3.11
RUN_IN_2: JD5.22, JD6.21, JD6.22
S0_MUX: JD2.28, JD3.14, MUX.20 (S0)
S1_MUX: JD2.30, JD3.15, MUX.21 (S1)
S2_MUX: JD2.32, JD3.16, MUX.22 (S2)
S3_MUX: JD2.34, JD3.17, MUX.23 (S3)
SCL_BMP: BMP280.5, BMP280.6, JS2.23, JS3.12
SCL_TSL: JS2.9, JS3.5, TSL2561.5, TSL2561.6
SDA_BMP: BMP280.7, BMP280.8, JS2.21, JS3.11
SDA_TSL: JS2.7, JS3.4, TSL2561.3, TSL2561.4
SDO_BMP: BMP280.11, BMP280.12
SIG_ADC: JD2.18, JD2.20, JD3.9, JD3.10, MUX.24 (SIG)
SWCLK: UC_SENZORI.D1 (SWCLK)
SWCLK_2: UC_EXTRA.D1 (SWCLK)
SWDIO: UC_SENZORI.D3 (SWDIO)
SWDIO_2: UC_EXTRA.D3 (SWDIO)
TP1: UC_SENZORI.TP1 (TP1_GND)
TP1_2: UC_EXTRA.TP1 (TP1_GND)
TP2: UC_SENZORI.TP2 (TP2_USB_DM)
TP2_2: UC_EXTRA.TP2 (TP2_USB_DM)
TP3: UC_SENZORI.TP3 (TP3_USB_DP)
TP3_2: UC_EXTRA.TP3 (TP3_USB_DP)
TP5: UC_SENZORI.TP5 (TP5_GPIO25/LED)
TP5_2: UC_EXTRA.TP5 (TP5_GPIO25/LED)
TP6: UC_SENZORI.TP6 (TP6_BOOTSEL)
TP6_2: UC_EXTRA.TP6 (TP6_BOOTSEL)
UART0_RX: JD2.38, JD3.19
UART0_RX_2: JD5.38, JD6.37, JD6.38
UART0_TX: JD2.40, JD3.20
UART0_TX_2: JD5.40, JD6.39, JD6.40
VBUS: JD1.1, JD2.1, UC_SENZORI.40 (VBUS)
VBUS_2: JD4.1, JD5.1, UC_EXTRA.40 (VBUS)
VBUS_2_OUT: JD5.2, JD6.1, JD6.2
VBUS_OUT: JD2.2, JD3.1
VSYS: JD1.2, JD2.3, UC_SENZORI.39 (VSYS)
VSYS_2: JD4.2, JD5.3, UC_EXTRA.39 (VSYS)

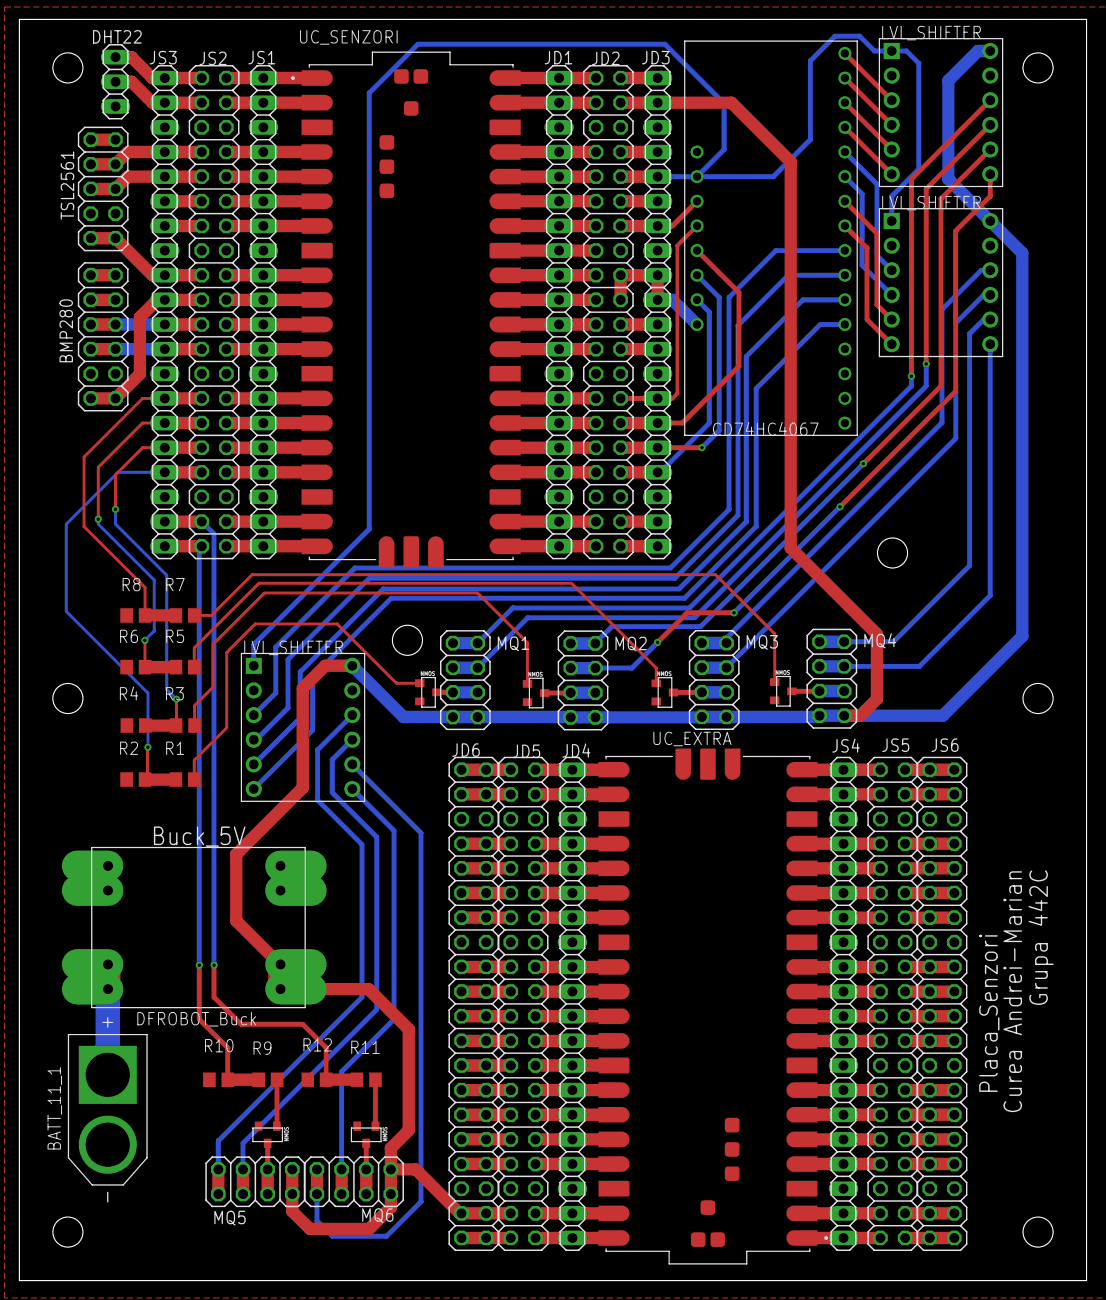
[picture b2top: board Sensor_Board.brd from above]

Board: 2 copper layers, 110.0 x 130.0 mm, 47 parts (0 on the bottom side), 169 nets.

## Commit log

2023-12-22 README.md
2023-12-22 Added Files from project to Public Repo
